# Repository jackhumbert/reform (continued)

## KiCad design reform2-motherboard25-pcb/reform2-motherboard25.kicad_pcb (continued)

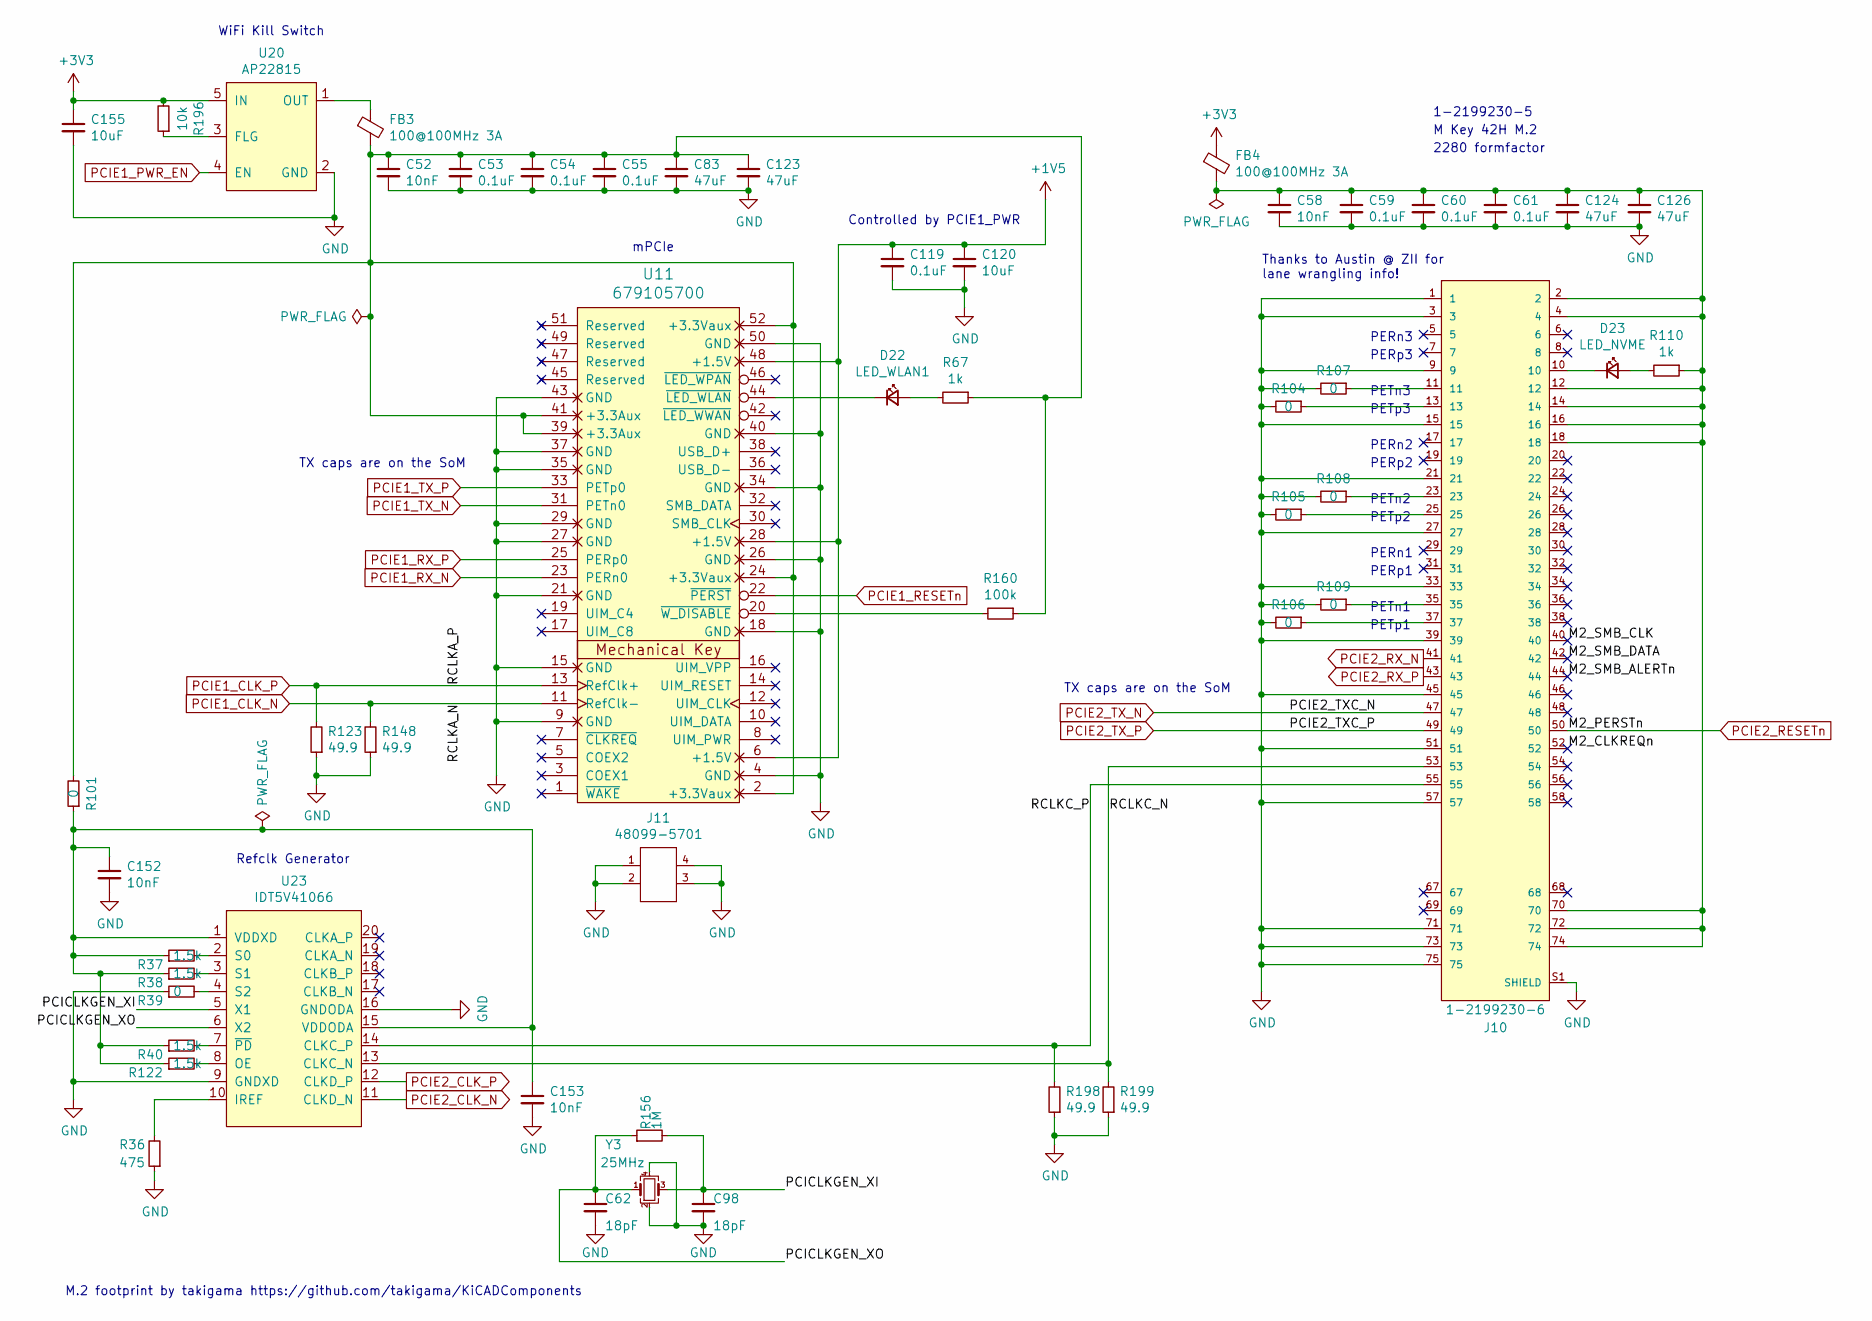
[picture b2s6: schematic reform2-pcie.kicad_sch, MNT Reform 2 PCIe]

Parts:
C52, C58, C152, C153: 10nF; C_0603_1608Metric
C53, C54, C55, C59, C60, C61, C119: 0.1uF; C_0603_1608Metric
C62, C98: 18pF; C_0603_1608Metric
C83, C123, C124, C126: 47uF; C_0603_1608Metric
C120, C155: 10uF; C_0603_1608Metric
D22: LED_WLAN1; LED_0603_1608Metric
D23: LED_NVME; LED_0603_1608Metric
FB3, FB4: 100@100MHz 3A; L_0603_1608Metric
J10: 1-2199230-6; TE_1-2199230-6
J11: 48099-5701; MOLEX_48099-5701
R36: 475; R_0603_1608Metric
R37, R38, R40, R122: 1.5k; R_0603_1608Metric
R39, R101, R104, R105, R106, R107, R108, R109: 0; R_0603_1608Metric
R67, R110: 1k; R_0603_1608Metric
R123, R148, R198, R199: 49.9; R_0603_1608Metric
R156: 1M; R_0603_1608Metric
R160: 100k; R_0603_1608Metric
R196: 10k; R_0603_1608Metric
U11: 679105700; MOLEX_67910-5700
U20: AP22815; TSOT-25
U23: IDT5V41066; TSSOP-20_4.4x6.5mm_P0.65mm
Y3: 25MHz; Crystal_SMD_Abracon_ABM8G-4Pin_3.2x2.5mm

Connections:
+1V5: C119.1, C120.1, U11.6 (+1.5V), U11.28 (+1.5V), U11.48 (+1.5V); also elsewhere on the board
+3V3: C155.1, FB4.1, R196.2, U20.5 (IN); also elsewhere on the board
/Reform 2 PCIe/M2_CLKREQn: J10.52
/Reform 2 PCIe/M2_SMB_ALERTn: J10.44
/Reform 2 PCIe/M2_SMB_CLK: J10.40
/Reform 2 PCIe/M2_SMB_DATA: J10.42
/Reform 2 PCIe/PCICLKGEN_XI: C98.1, R156.2, U23.5 (X1), Y3.3
/Reform 2 PCIe/PCICLKGEN_XO: C62.1, R156.1, U23.6 (X2), Y3.1
/Reform 2 PCIe/RCLKC_N: J10.53, R199.2, U23.13 (CLKC_N)
/Reform 2 PCIe/RCLKC_P: J10.55, R198.2, U23.14 (CLKC_P)
GND: C52.2, C53.2, C54.2, C55.2, C58.2, C59.2, C60.2, C61.2, C62.2, C83.2, C98.2, C119.2, C120.2, C123.2, C124.2, C126.2, C152.2, C153.2, C155.2, J10.1, J10.3, J10.9, J10.15, J10.21, J10.27, J10.33, J10.39, J10.45, J10.51, J10.57, J10.71, J10.73, J10.75, J10.S1 (SHIELD), J10.S2 (SHIELD), J11.1, J11.2, J11.3, J11.4, R36.1, R39.1, R104.2, R105.2, R106.2, R107.2, R108.2, R109.2, R123.1, R148.1, R198.1, R199.1, U11.4 (GND), U11.9 (GND), U11.15 (GND), U11.18 (GND), U11.21 (GND), U11.26 (GND), U11.27 (GND), U11.29 (GND), U11.34 (GND), U11.35 (GND), U11.37 (GND), U11.40 (GND), U11.43 (GND), U11.50 (GND), U20.2 (GND), U23.9 (GNDXD), U23.16 (GNDODA), Y3.2, Y3.4; also elsewhere on the board
unnamed: C52.1, C53.1, C54.1, C55.1, C83.1, C123.1, FB3.2, R67.1, R101.2, R160.1, U11.2 (+3.3Vaux), U11.24 (+3.3Vaux), U11.39 (+3.3Aux), U11.41 (+3.3Aux), U11.52 (+3.3Vaux)
unnamed: C58.1, C59.1, C60.1, C61.1, C124.1, C126.1, FB4.2, J10.2, J10.4, J10.12, J10.14, J10.16, J10.18, J10.70, J10.72, J10.74, R110.1
unnamed: C152.1, C153.1, R37.1, R38.1, R40.1, R101.1, R122.1, U23.1 (VDDXD), U23.15 (VDDODA)
unnamed: D22.1 (K), U11.44 (~LED_WLAN)
unnamed: D22.2 (A), R67.2
unnamed: D23.1 (K), J10.10
unnamed: D23.2 (A), R110.2
unnamed: J10.11, R107.1
unnamed: J10.13, R104.1
unnamed: J10.23, R108.1
unnamed: J10.25, R105.1
unnamed: J10.35, R109.1
unnamed: J10.37, R106.1
unnamed: R36.2, U23.10 (IREF)
unnamed: R37.2, U23.2 (S0)
unnamed: R38.2, U23.3 (S1)
unnamed: R39.2, U23.4 (S2)
unnamed: R40.2, U23.7 (~PD)
unnamed: R122.2, U23.8 (OE)
unnamed: R160.2, U11.20 (~W_DISABLE)
unnamed: R196.1, U20.3 (FLG)
unnamed: FB3.1, U20.1 (OUT)
PCIE1_CLK_N: R148.2, U11.11 (RefClk-); also elsewhere on the board
PCIE1_CLK_P: R123.2, U11.13 (RefClk+); also elsewhere on the board
PCIE1_PWR_EN: U20.4 (EN); also elsewhere on the board
PCIE1_RESETn: U11.22 (~PERST); also elsewhere on the board
PCIE1_RX_N: U11.23 (PERn0); also elsewhere on the board
PCIE1_RX_P: U11.25 (PERp0); also elsewhere on the board
PCIE1_TX_N: U11.31 (PETn0); also elsewhere on the board
PCIE1_TX_P: U11.33 (PETp0); also elsewhere on the board
PCIE2_CLK_N: U23.11 (CLKD_N); also elsewhere on the board
PCIE2_CLK_P: U23.12 (CLKD_P); also elsewhere on the board
PCIE2_RESETn: J10.50; also elsewhere on the board
PCIE2_RX_N: J10.41; also elsewhere on the board
PCIE2_RX_P: J10.43; also elsewhere on the board
PCIE2_TX_N: J10.47; also elsewhere on the board
PCIE2_TX_P: J10.49; also elsewhere on the board

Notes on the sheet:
1-2199230-5
Controlled by PCIE1_PWR
Thanks to Austin @ ZII for lane wrangling info!
PERp1
PERn3
TX caps are on the SoM
M.2 footprint by takigama https://github.com/takigama/KiCADComponents
PETn3
PETn1
2280 formfactor
Refclk Generator
PETp2
PETn2
PERp2
M Key 42H M.2
PERn2
mPCIe
PERp3
WiFi Kill Switch
PETp1
PERn1
PETp3

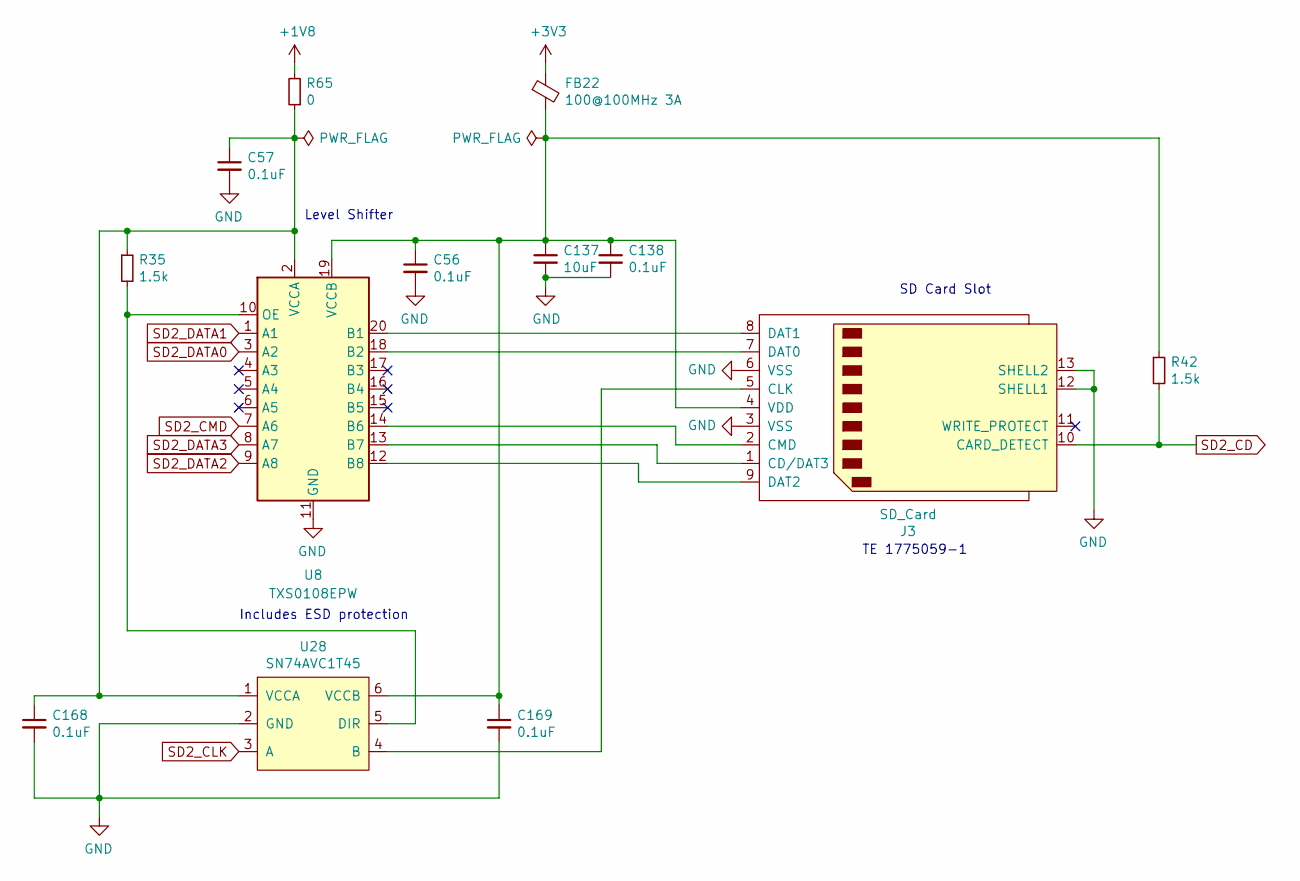
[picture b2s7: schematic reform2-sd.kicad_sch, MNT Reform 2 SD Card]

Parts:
C56, C57, C138, C168, C169: 0.1uF; C_0603_1608Metric
C137: 10uF; C_0603_1608Metric
FB22: 100@100MHz 3A; L_0603_1608Metric
J3: SD_Card; TE_1775059-1
R35, R42: 1.5k; R_0603_1608Metric
R65: 0; R_0603_1608Metric
U8: TXS0108EPW; TSSOP-20_4.4x6.5mm_P0.65mm
U28: SN74AVC1T45; SOT-23-6

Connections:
+1V8: R65.2; also elsewhere on the board
+3V3: FB22.1; also elsewhere on the board
GND: C56.2, C57.2, C137.2, C138.2, C168.2, C169.2, J3.3 (VSS), J3.6 (VSS), J3.12 (SHELL1), J3.13 (SHELL2), U8.11 (GND), U28.2 (GND); also elsewhere on the board
unnamed: C56.1, C137.1, C138.1, C169.1, FB22.2, J3.4 (VDD), R42.1, U8.19 (VCCB), U28.6 (VCCB)
unnamed: C57.1, C168.1, R35.1, R65.1, U8.2 (VCCA), U28.1 (VCCA)
unnamed: J3.1 (CD/DAT3), U8.13 (B7)
unnamed: J3.2 (CMD), U8.14 (B6)
unnamed: J3.5 (CLK), U28.4 (B)
unnamed: J3.7 (DAT0), U8.18 (B2)
unnamed: J3.8 (DAT1), U8.20 (B1)
unnamed: J3.9 (DAT2), U8.12 (B8)
unnamed: R35.2, U8.10 (OE), U28.5 (DIR)
SD2_CD: J3.10 (CARD_DETECT), R42.2; also elsewhere on the board
SD2_CLK: U28.3 (A); also elsewhere on the board
SD2_CMD: U8.7 (A6); also elsewhere on the board
SD2_DATA0: U8.3 (A2); also elsewhere on the board
SD2_DATA1: U8.1 (A1); also elsewhere on the board
SD2_DATA2: U8.9 (A8); also elsewhere on the board
SD2_DATA3: U8.8 (A7); also elsewhere on the board

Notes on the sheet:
TE 1775059-1
SD Card Slot
Level Shifter
Includes ESD protection

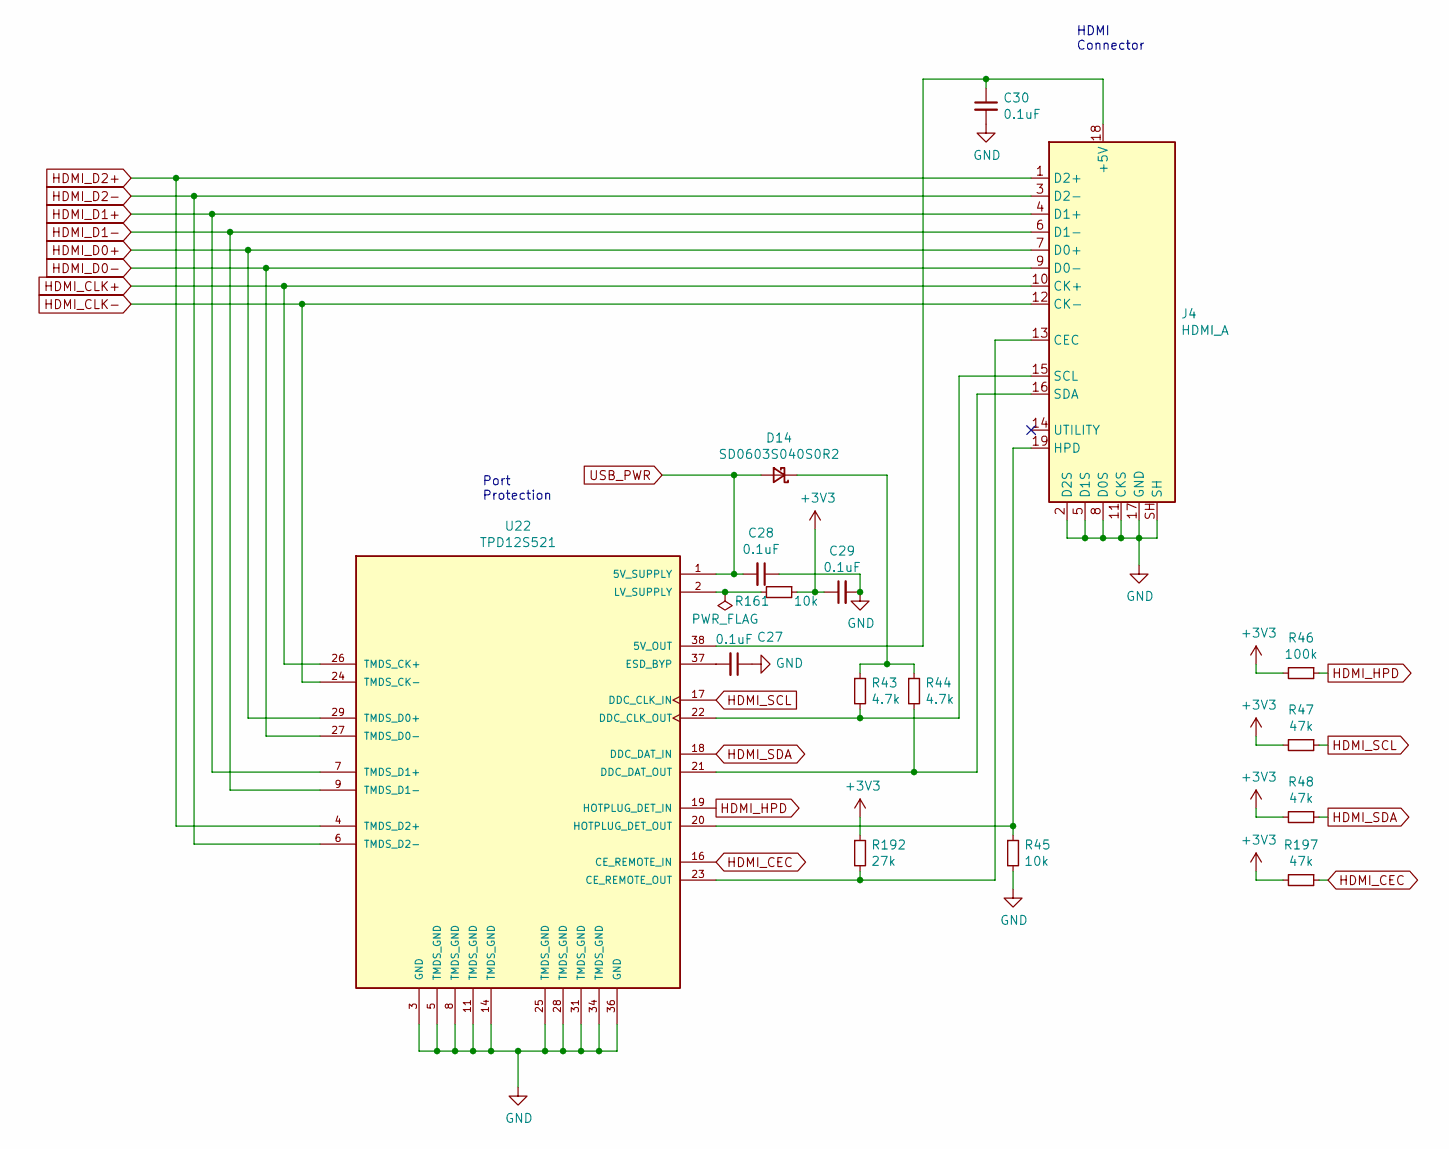
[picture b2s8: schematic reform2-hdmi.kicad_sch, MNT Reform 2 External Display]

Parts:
C27, C28, C29, C30: 0.1uF; C_0603_1608Metric
D14: SD0603S040S0R2; D_0603_1608Metric_Castellated
J4: HDMI_A; HDMI-685119134923
R43, R44: 4.7k; R_0603_1608Metric
R45, R161: 10k; R_0603_1608Metric
R46: 100k; R_0603_1608Metric
R47, R48, R197: 47k; R_0603_1608Metric
R192: 27k; R_0603_1608Metric
U22: TPD12S521; TSSOP50P640X120-38N

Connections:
+3V3: C29.1, R46.2, R47.2, R48.2, R161.1, R192.1, R197.2; also elsewhere on the board
GND: C27.1, C28.1, C29.2, C30.2, J4.2 (D2S), J4.5 (D1S), J4.8 (D0S), J4.11 (CKS), J4.17 (GND), J4.SH, R45.2, U22.3 (GND), U22.5 (TMDS_GND), U22.8 (TMDS_GND), U22.11 (TMDS_GND), U22.14 (TMDS_GND), U22.25 (TMDS_GND), U22.28 (TMDS_GND), U22.31 (TMDS_GND), U22.34 (TMDS_GND), U22.36 (GND); also elsewhere on the board
HDMI_CEC: R197.1, U22.16 (CE_REMOTE_IN); also elsewhere on the board
HDMI_CLK+: J4.10 (CK+), U22.13 (TMDS_CK+), U22.26 (TMDS_CK+); also elsewhere on the board
HDMI_CLK-: J4.12 (CK-), U22.15 (TMDS_CK-), U22.24 (TMDS_CK-); also elsewhere on the board
HDMI_D0+: J4.7 (D0+), U22.10 (TMDS_D0+), U22.29 (TMDS_D0+); also elsewhere on the board
HDMI_D0-: J4.9 (D0-), U22.12 (TMDS_D0-), U22.27 (TMDS_D0-); also elsewhere on the board
HDMI_D1+: J4.4 (D1+), U22.7 (TMDS_D1+), U22.32 (TMDS_D1+); also elsewhere on the board
HDMI_D1-: J4.6 (D1-), U22.9 (TMDS_D1-), U22.30 (TMDS_D1-); also elsewhere on the board
HDMI_D2+: J4.1 (D2+), U22.4 (TMDS_D2+), U22.35 (TMDS_D2+); also elsewhere on the board
HDMI_D2-: J4.3 (D2-), U22.6 (TMDS_D2-), U22.33 (TMDS_D2-); also elsewhere on the board
HDMI_HPD: R46.1, U22.19 (HOTPLUG_DET_IN); also elsewhere on the board
HDMI_SCL: R47.1, U22.17 (DDC_CLK_IN); also elsewhere on the board
HDMI_SDA: R48.1, U22.18 (DDC_DAT_IN); also elsewhere on the board
unnamed: C27.2, U22.37 (ESD_BYP)
unnamed: C30.1, J4.18 (+5V), U22.38 (5V_OUT)
unnamed: D14.1 (K), R43.1, R44.1
unnamed: J4.13 (CEC), R192.2, U22.23 (CE_REMOTE_OUT)
unnamed: J4.15 (SCL), R43.2, U22.22 (DDC_CLK_OUT)
unnamed: J4.16 (SDA), R44.2, U22.21 (DDC_DAT_OUT)
unnamed: J4.19 (HPD), R45.1, U22.20 (HOTPLUG_DET_OUT)
unnamed: R161.2, U22.2 (LV_SUPPLY)
USB_PWR: C28.2, D14.2 (A), U22.1 (5V_SUPPLY); also elsewhere on the board

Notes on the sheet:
HDMI Connector
Port Protection

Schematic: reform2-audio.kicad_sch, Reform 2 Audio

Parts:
C127, C147: 220uF; C_1210_3225Metric
C139, C151, C170: 4.7uF; C_0603_1608Metric
C141, C162, C163: 1uF; C_0603_1608Metric
C142, C143, C144, C154, C156, C158, C165, C166: 0.1uF; C_0603_1608Metric
C150: 10uF; C_0603_1608Metric
C157, C159: 470nF; C_0603_1608Metric
D10: SP0503BAHT; SOT-143
FB10, FB11, FB16, FB17, FB18, FB19, FB20, FB21: 100@100MHz 3A; L_0603_1608Metric
J7: SJ-43516-SMT
J16: LINE_IN; PinHeader_1x03_P2.00mm_Vertical
J21: Conn_01x04; JST_PH_B4B-PH-K_1x04_P2.00mm_Vertical
L8, L9, L10, L11: 15uH; L_1210_3225Metric
R66, R112: 220; R_0603_1608Metric
R114, R121, R138, R139, R150, R151: 33; R_0603_1608Metric
R135, R136: 4.7k; R_0603_1608Metric
R140: 680; R_0603_1608Metric
R141, R152, R187: 0; R_0603_1608Metric
R142, R143, R144: 47k; R_0603_1608Metric
U3: WM8960; QFN-32-1EP_5x5mm_P0.5mm_EP3.45x3.45mm_ThermalVias

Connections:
+3V3: FB18.1, FB20.1, FB21.1, R135.1, R136.1, R187.1; also elsewhere on the board
DAC_BCLK: R114.1; also elsewhere on the board
DAC_DIN: R150.1; also elsewhere on the board
DAC_DOUT: R121.1; also elsewhere on the board
DAC_MCLK: R138.2; also elsewhere on the board
DAC_RXFS: R139.1; also elsewhere on the board
DAC_SCL: R66.1; also elsewhere on the board
DAC_SDA: R112.1; also elsewhere on the board
DAC_TXFS: R151.1; also elsewhere on the board
GND: C139.2, C142.2, C143.2, C144.1, C150.2, C151.2, C154.2, C156.2, C158.2, C165.2, C166.2, C170.2, D10.1 (A), J7.4 (RING2), J16.1, R142.2, R143.2, U3.9 (DGND), U3.20 (SPKGND2), U3.24 (SPKGND1), U3.28 (AGND), U3.33 (GND); also elsewhere on the board
unnamed: C127.1, D10.3 (K), J7.2 (TIP), R142.1
unnamed: C127.2, U3.31 (HP_L)
unnamed: C139.1, C151.1, FB19.2, U3.21 (SPKVDD2), U3.26 (SPKVDD1)
unnamed: C141.1, D10.2 (K), J7.1 (SLEEVE), R140.2
unnamed: C141.2, U3.4 (LINPUT1)
unnamed: C142.1, FB21.2, U3.32 (AVDD)
unnamed: C143.1, FB20.2, R144.1, U3.10 (DBVDD)
unnamed: C144.2, FB18.2, U3.8 (DCVDD)
unnamed: C147.1, D10.4 (K), J7.3 (RING1), R143.1
unnamed: C147.2, U3.29 (HP_R)
unnamed: C150.1, C154.1, U3.27 (VMID)
unnamed: C156.1, C157.1, J21.4, L8.2
unnamed: C157.2, C158.1, J21.3, L9.2
unnamed: C159.1, C165.1, J21.2, L10.2
unnamed: C159.2, C166.1, J21.1, L11.2
unnamed: C162.1, U3.3 (LINPUT2)
unnamed: C162.2, J16.3
unnamed: C163.1, U3.6 (RINPUT2)
unnamed: C163.2, J16.2
unnamed: C170.1, R140.1, U3.1 (MICBIAS)
unnamed: J7.6 (RING_SWITCH), R141.1, R144.2
unnamed: FB10.2, L8.1
unnamed: FB11.2, L9.1
unnamed: FB16.2, L10.1
unnamed: FB17.2, L11.1
unnamed: R112.2, R136.2, U3.18 (SDIN)
unnamed: R114.2, U3.12 (BCLK)
unnamed: R121.2, U3.14 (DACDAT)
unnamed: R66.2, R135.2, U3.17 (SCLK)
unnamed: R138.1, U3.11 (MCLK)
unnamed: R139.2, U3.15 (ADCLRC)
unnamed: R141.2, U3.2 (LINPUT3)
unnamed: R150.2, U3.16 (ADCDAT)
unnamed: R151.2, U3.13 (DACLRC)
unnamed: FB19.1, R152.2, R187.2
unnamed: FB17.1, U3.19 (SPK_RN)
unnamed: FB16.1, U3.22 (SPK_RP)
unnamed: FB11.1, U3.23 (SPK_LN)
unnamed: FB10.1, U3.25 (SPK_LP)
USB_PWR: R152.1; also elsewhere on the board

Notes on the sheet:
CTIA standard TRRS
butterworth filter with 40khz cutoff: speaker ohms = 8 L = 22.5uH C = 0.35uF
Jack Detect
Audio Codec
Speakers: PUI AS01808AO-3-R 8 Ohm 1 W
NOSTUFF
NOTE: DCVDD could be 1.8v
more bass!
800mA

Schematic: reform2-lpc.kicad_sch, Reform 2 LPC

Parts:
BT1: CR1220; BatteryHolder_Keystone_3000_1x12mm
C46, C47: 10uF; C_0603_1608Metric
C48, C51: 18pF; C_0603_1608Metric
C49, C50, C140: 0.1uF; C_0603_1608Metric
J8: USB_C_Receptacle_USB2.0; USB_C_Receptacle_HRO_TYPE-C-31-M-12
J22: LPC_IO; PinHeader_2x08_P2.54mm_Vertical
J23: KDBSYSCTL; JST_PH_B4B-PH-K_1x04_P2.00mm_Vertical
R68, R69: 4.7k; R_0603_1608Metric
R70, R72: 33; R_0603_1608Metric
R71, R195: 1.5k; R_0603_1608Metric
R73, R74, R75, R76, R124, R125, R126, R137, R157, R194: 0; R_0603_1608Metric
R128: 10k; R_0603_1608Metric
SW1: SW_DIP_x01; SW_DIP_SPSTx01_Slide_Omron_A6S-110x_W8.9mm_P2.54mm
SW2: SW_Push; UK-B0206-G3.8-250-JZ
U5: PCF8523T; SOIC-8_3.9x4.9mm_P1.27mm
U18: LPC11U24FBD48-301; LQFP-48_7x7mm_P0.5mm
Y2: 12MHz; Crystal_SMD_Abracon_ABM8G-4Pin_3.2x2.5mm
Y4: 32.768 kHz; Crystal_SMD_3215-2Pin_3.2x1.5mm

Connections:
1V2_PWR_EN: U18.2 (PIO1_19); also elsewhere on the board
3V3_PWR_EN: U18.48 (PIO1_16); also elsewhere on the board
5V_PWR_EN: U18.43 (PIO1_15); also elsewhere on the board
/Reform 2 Power/Reform 2 LPC/LPCUD_N: R72.2, U18.19 (USB_DM)
/Reform 2 Power/Reform 2 LPC/LPCUD_P: R70.2, U18.20 (USB_DP)
/Reform 2 Power/Reform 2 LPC/LPC_AD5: J22.7, U18.40 (PIO0_16)
/Reform 2 Power/Reform 2 LPC/LPC_AD7: J22.10, U18.42 (PIO0_23)
/Reform 2 Power/Reform 2 LPC/LPC_MISO0: R124.1, U18.27 (PIO0_8)
/Reform 2 Power/Reform 2 LPC/LPC_MISO1a: J22.2, U18.30 (PIO0_22)
/Reform 2 Power/Reform 2 LPC/LPC_MISO1b: R74.2, U18.26 (PIO1_21)
/Reform 2 Power/Reform 2 LPC/LPC_MOSI0: R125.1, U18.28 (PIO0_9)
/Reform 2 Power/Reform 2 LPC/LPC_MOSI1a: J22.14, U18.17 (PIO0_21)
/Reform 2 Power/Reform 2 LPC/LPC_MOSI1b: R75.2, U18.38 (PIO1_22)
/Reform 2 Power/Reform 2 LPC/LPC_RXDa: J22.12, U18.46 (PIO0_18)
/Reform 2 Power/Reform 2 LPC/LPC_RXDc: J23.3, U18.11 (PIO1_26)
/Reform 2 Power/Reform 2 LPC/LPC_SCK0a: R126.1, U18.29 (PIO0_10)
/Reform 2 Power/Reform 2 LPC/LPC_SCK0b: J22.1, U18.31 (PIO1_29)
/Reform 2 Power/Reform 2 LPC/LPC_SCK1b: R73.2, U18.13 (PIO1_20)
/Reform 2 Power/Reform 2 LPC/LPC_SCLKa: J22.9, U18.45 (PIO0_17)
/Reform 2 Power/Reform 2 LPC/LPC_SCLKc: R194.2, U18.24 (PIO1_28)
/Reform 2 Power/Reform 2 LPC/LPC_SSEL0: R157.1, U18.10 (PIO0_2)
/Reform 2 Power/Reform 2 LPC/LPC_SSEL1: R76.2, U18.18 (PIO1_23)
/Reform 2 Power/Reform 2 LPC/LPC_SWDIO: J22.8, U18.39 (PIO0_15)
/Reform 2 Power/Reform 2 LPC/LPC_TDI: J22.4, U18.32 (PIO0_11)
/Reform 2 Power/Reform 2 LPC/LPC_TDO: J22.6, U18.34 (PIO0_13)
/Reform 2 Power/Reform 2 LPC/LPC_TMS: J22.3, U18.33 (PIO0_12)
/Reform 2 Power/Reform 2 LPC/LPC_TXDa: J22.11, U18.47 (PIO0_19)
/Reform 2 Power/Reform 2 LPC/LPC_TXDc: J23.2, U18.12 (PIO1_27)
/Reform 2 Power/Reform 2 LPC/LPC_UFTOGG: SW1.2, U18.4 (PIO0_1)
/Reform 2 Power/Reform 2 LPC/LPC_UVBUS: R195.2, U18.14 (PIO0_3)
/Reform 2 Power/Reform 2 LPC/LPC_~RESET: SW2.2, U18.3 (PIO0_0)
/Reform 2 Power/Reform 2 LPC/LPC_~TRST: J22.5, U18.35 (PIO0_14)
/Reform 2 Power/Reform 2 LPC/LPC_~USBCON: J22.13, U18.22 (PIO0_6)
AUX_PWR_EN: U18.23 (PIO0_7); also elsewhere on the board
BMON_CS: R76.1; also elsewhere on the board
BMON_SCK: R73.1; also elsewhere on the board
BMON_SDI: R75.1; also elsewhere on the board
BMON_SDO: R74.1, R128.1; also elsewhere on the board
CHG_RNG: U18.1 (PIO1_25); also elsewhere on the board
DAC_SCL: U5.6 (SCL); also elsewhere on the board
DAC_SDA: U5.5 (SDA); also elsewhere on the board
GND: BT1.2 (-), C46.2, C47.2, C48.2, C49.2, C50.2, C51.2, C140.1, J8.A1 (GND), J8.A12 (GND), J8.B1 (GND), J8.B12 (GND), J8.S1 (SHIELD), J22.16, J23.4, SW1.1, SW2.1, U5.4 (VSS), U18.5 (VSS), U18.41 (VSS), Y2.2, Y2.4; also elsewhere on the board
IMX_RESETn: R194.1; also elsewhere on the board
IMX_RTC_IRQ: R137.1; also elsewhere on the board
IMX_WAKE: U18.21 (PIO1_24); also elsewhere on the board
INA_SCL: R69.2, U18.15 (PIO0_4); also elsewhere on the board
INA_SDA: R68.2, U18.16 (PIO0_5); also elsewhere on the board
LPC_MISO: R124.2; also elsewhere on the board
LPC_MOSI: R125.2; also elsewhere on the board
LPC_SCK: R126.2; also elsewhere on the board
LPC_SS0: R157.2; also elsewhere on the board
LPC_UART2_RX: U18.37 (PIO1_14); also elsewhere on the board
LPC_UART2_TX: U18.36 (PIO1_13); also elsewhere on the board
LPC_VCC: C46.1, C47.1, C49.1, C50.1, C140.2, J22.15, J23.1, R68.1, R69.1, R71.1, R128.2, R195.1, U5.8 (VDD), U18.8 (VDD), U18.44 (VDD); also elsewhere on the board
unnamed: BT1.1 (+), U5.3 (VBAT)
unnamed: C48.1, U18.7 (XTALOUT), Y2.1
unnamed: C51.1, U18.6 (XTALIN), Y2.3
unnamed: J8.A6 (D+), J8.B6 (D+), R70.1, R71.2
unnamed: J8.A7 (D-), J8.B7 (D-), R72.1
unnamed: R137.2, U5.7 (~INT1/CLKOUT)
unnamed: U5.1 (OSCI), Y4.1
unnamed: U5.2 (OSCO), Y4.2
PCIE1_PWR_EN: U18.9 (PIO0_20); also elsewhere on the board
USB_PWR_EN: U18.25 (PIO1_31); also elsewhere on the board

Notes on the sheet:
TODO: check CCs
System Controller
Expansion Port
I2C lines pulled up by SYS 3v3 power near DAC
Power Switches
Keyboard System Control Port (SYSCTL)
Powered by coin cell when batteries removed
Powered by main batteries in standby
Realtime Clock

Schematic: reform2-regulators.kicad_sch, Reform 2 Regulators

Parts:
C3: 0.33uF; C_0603_1608Metric
C16, C17: 100uF; CP_Elec_8x10
C18, C19: 220uF; CP_Elec_8x10
C33, C35: 4.7uF; C_0603_1608Metric
C34, C37: 10uF; C_0603_1608Metric
C36, C38: 6.8pF; C_0603_1608Metric
C82: 2.2uF; C_0603_1608Metric
C121: 47uF; C_0603_1608Metric
C128, C148: 10nF; C_0603_1608Metric
C129, C130, C145, C146: 1uF; C_0603_1608Metric
D3: SBR0560S1; D_SOD-123
D11: LED3V; LED_0603_1608Metric
D12: LED5V; LED_0603_1608Metric
D15, D16: BZX584C3V3-G3-08; D_SOD-523
D20, D21: SK54A-LTP; D_SMA
L3, L4: 68uH; L_Bourns_SRR1210A
L5: 10uH; L_1210_3225Metric
L6, L7: 2.2uH; L_1210_3225Metric
R1: 1M; R_0603_1608Metric
R33, R164: 1k; R_0603_1608Metric
R53, R57: 51k; R_0603_1608Metric
R58: 68k; R_0603_1608Metric
R98, R100, R185, R186: 0; R_0603_1608Metric
R178, R179, R181, R188, R189: 100k; R_0603_1608Metric
R180: 150k; R_0603_1608Metric
U7: LM2677SX-5; TO-263-7_TabPin8
U12: LM2677SX-3.3; TO-263-7_TabPin8
U13, U19: TLV62568DBV; SOT-23-5
U14: LMR16006YQ3; TSOT-23-6
U17: TLV1117-18; SOT-223

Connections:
1V2_PWR_EN: R185.1; also elsewhere on the board
3V3_PWR_AUX: R98.2; also elsewhere on the board
3V3_PWR_EN: D16.1 (K), R57.2, U12.7 (ON/~OFF); also elsewhere on the board
5V_PWR_EN: D15.1 (K), R53.2, U7.7 (ON/~OFF); also elsewhere on the board
30V_GATE: C16.1, C17.1, C82.2, C145.2, C146.2, R1.2, U7.2 (VIN), U12.2 (VIN), U14.5 (VIN); also elsewhere on the board
+1V2: C36.1, C37.1, L6.2, R178.1; also elsewhere on the board
+1V5: C34.1, C38.1, L7.2, R180.1; also elsewhere on the board
+1V8: C130.1, U17.2 (VO); also elsewhere on the board
+3V3: C19.1, D11.2 (A), L4.2, R100.2, U12.6 (FB); also elsewhere on the board
+5V: C18.1, C33.1, C35.1, D12.2 (A), L3.2, U7.6 (FB), U13.4 (VIN), U19.4 (VIN); also elsewhere on the board
GND: C16.2, C17.2, C18.2, C19.2, C33.2, C34.2, C35.2, C37.2, C82.1, C121.1, C129.2, C130.2, C145.1, C146.1, D3.2 (A), D15.2 (A), D16.2 (A), D20.2 (A), D21.2 (A), R33.1, R53.1, R57.1, R58.2, R164.1, R179.2, R181.2, R188.2, R189.2, U7.4 (GND), U7.8 (PAD), U12.4 (GND), U12.8 (PAD), U13.2 (GND), U14.2 (GND), U17.1 (GND), U19.2 (GND); also elsewhere on the board
LPC_VCC: C121.2, L5.2, U14.3 (FB); also elsewhere on the board
unnamed: C3.1, D3.1 (K), L5.1, U14.6 (SW)
unnamed: C3.2, U14.1 (BOOST)
unnamed: C36.2, R178.2, R179.1, U13.5 (FB)
unnamed: C38.2, R180.2, R181.1, U19.5 (FB)
unnamed: C128.1, D21.1 (K), L4.1, U12.1 (VSW)
unnamed: C128.2, U12.3 (CB)
unnamed: C129.1, R98.1, R100.1, U17.3 (VI)
unnamed: C148.1, D20.1 (K), L3.1, U7.1 (VSW)
unnamed: C148.2, U7.3 (CB)
unnamed: D11.1 (K), R33.2
unnamed: D12.1 (K), R164.2
unnamed: L6.1, U13.3 (SW)
unnamed: L7.1, U19.3 (SW)
unnamed: R1.1, R58.1, U14.4 (EN)
unnamed: R185.2, R188.1, U13.1 (EN)
unnamed: R186.2, R189.1, U19.1 (EN)
PCIE1_PWR_EN: R186.1; also elsewhere on the board

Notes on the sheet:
Standby always-on 3V3 power rail
Power LEDs
TODO: test new UVLO <20V
NOSTUFF
Up to 1A (peak) 375mA normal from mPCIe
Up to 70mA consumed by DSI bridge
Up to 780mA (!) consumed by USB hub
Up to 5A @ 5V
TODO: test these!
Up to 5A @ 3.3V
VCCIO supply for DSI + SD
Up to 40mA consumed by DSI bridge and SD card level shifter
Main system power converters, enabled by LPC

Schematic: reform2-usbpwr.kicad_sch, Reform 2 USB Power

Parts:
C164, C167: 10uF; C_0603_1608Metric
R2, R83: 10k; R_0603_1608Metric
U24, U27: AP22815; TSOT-25

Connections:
3V3_PWR_AUX: U27.1 (OUT); also elsewhere on the board
+3V3: C167.1, R2.2, U27.5 (IN); also elsewhere on the board
+5V: C164.1, R83.2, U24.5 (IN); also elsewhere on the board
AUX_PWR_EN: U27.4 (EN); also elsewhere on the board
GND: C164.2, C167.2, U24.2 (GND), U27.2 (GND); also elsewhere on the board
unnamed: R2.1, U27.3 (FLG)
unnamed: R83.1, U24.3 (FLG)
USB_PWR: U24.1 (OUT); also elsewhere on the board
USB_PWR_EN: U24.4 (EN); also elsewhere on the board

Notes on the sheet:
3V3 Aux Power Switch
USB Power Switch

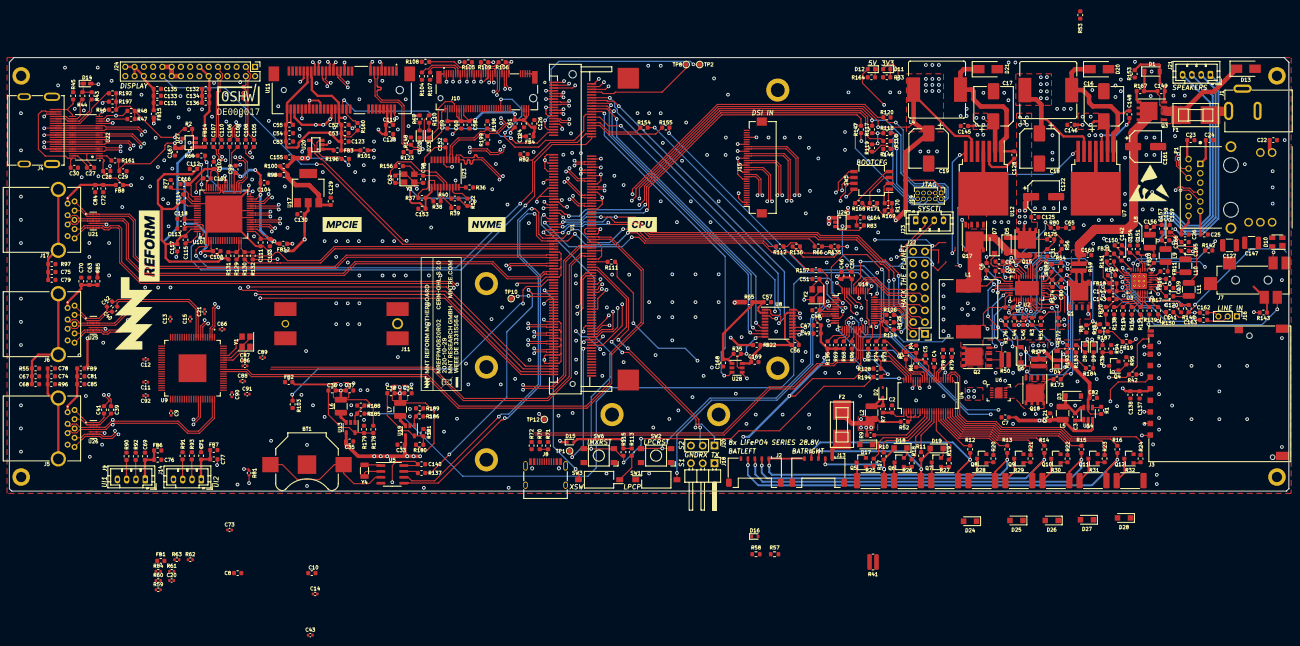
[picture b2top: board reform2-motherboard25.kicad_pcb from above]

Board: 6 copper layers, 276.0 x 93.5 mm, 504 parts (0 on the bottom side), 439 nets.

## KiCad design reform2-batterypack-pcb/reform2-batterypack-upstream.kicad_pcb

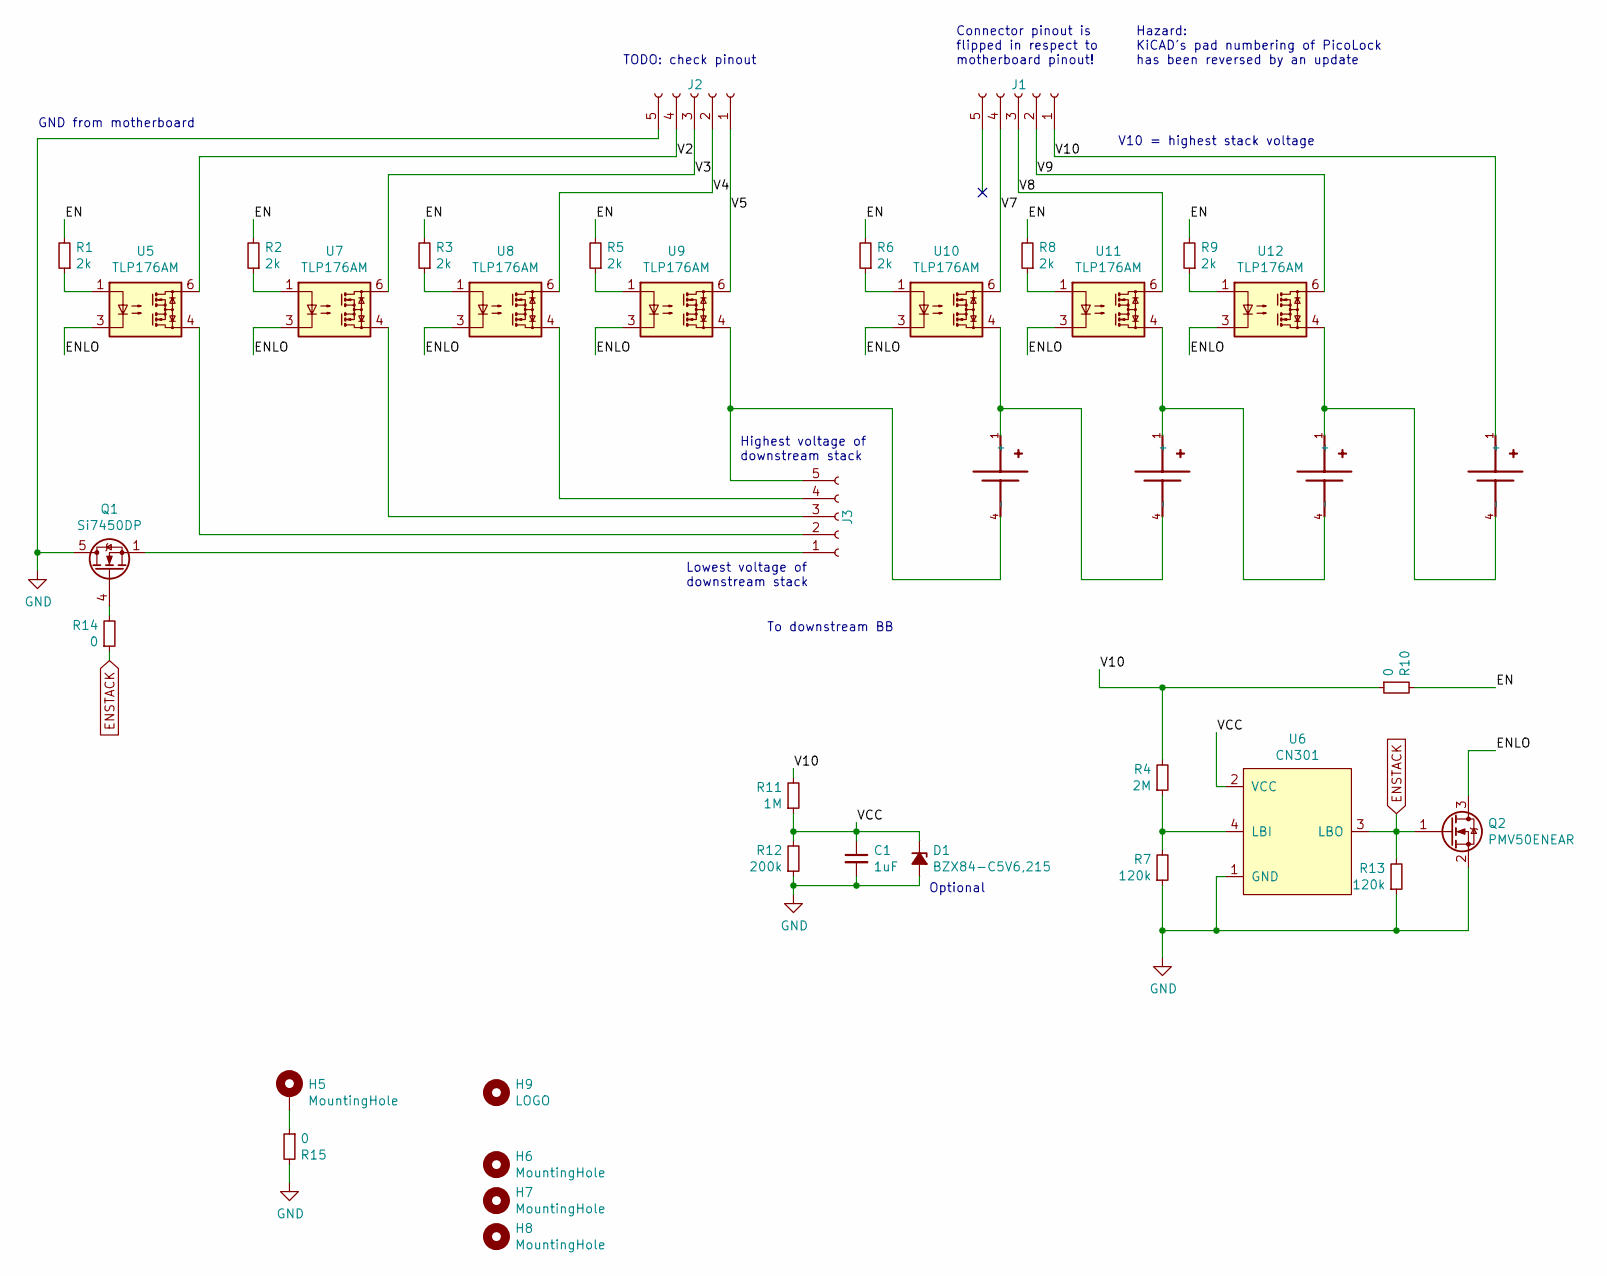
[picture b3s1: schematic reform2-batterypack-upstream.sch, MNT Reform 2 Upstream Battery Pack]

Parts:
C1: 1uF; C_0603_1608Metric
D1: BZX84-C5V6,215; D_SOT-23_ANK
H5, H6, H7, H8: MountingHole; MountingHole_2.2mm_M2
H9: LOGO; reform2-batterypack-badge-d5
J1, J2, J3: Conn_01x05_Female; Molex_Pico-Lock_504050-0591_1x05-1MP_P1.50mm_Horizontal
Q1: Si7450DP; PowerPAK_SO-8_Single
Q2: PMV50ENEAR; SOT-23
R1, R2, R3, R5, R6, R8, R9: 2k; R_0603_1608Metric
R4: 2M; R_0603_1608Metric
R7, R13: 120k; R_0603_1608Metric
R10, R14, R15: 0; R_0603_1608Metric
R11: 1M; R_0603_1608Metric
R12: 200k; R_0603_1608Metric
U1, U2, U3, U4: KEYSTONE_54; Keystone54
U5, U7, U8, U9, U10, U11, U12: TLP176AM; MFSOP6-4_4.4x3.6mm_P1.27mm
U6: CN301; SOT-23-5

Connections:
/EN: R1.2, R2.2, R3.2, R5.2, R6.2, R8.2, R9.2, R10.2
/ENLO: Q2.3 (D), U5.3, U7.3, U8.3, U9.3, U10.3, U11.3, U12.3
/V2: J2.4, U5.6
/V3: J2.3, U7.6
/V4: J2.2, U8.6
/V5: J2.1, U9.6
/V7: J1.4, U10.6
/V8: J1.3, U11.6
/V9: J1.2, U12.6
/V10: J1.1, R4.2, R10.1, R11.2, U4.1 (+), U4.2 (+), U4.3 (+)
/VCC: C1.1, D1.1 (K), R11.1, R12.2, U6.2 (VCC)
ENSTACK: Q1.4 (G), Q2.1 (G), R13.2, R14.1, R14.2, U6.3 (LBO)
GND: C1.2, D1.2 (A), J2.5, Q1.5 (D), Q2.2 (S), R7.1, R12.1, R13.1, R15.2, U6.1 (GND)
unnamed: J3.1, Q1.1 (S), Q1.2 (S), Q1.3 (S)
unnamed: J3.2, U5.4
unnamed: J3.3, U7.4
unnamed: J3.4, U8.4
unnamed: J3.5, U1.4 (-), U1.5 (-), U1.6 (-), U9.4
unnamed: R1.1, U5.1
unnamed: R2.1, U7.1
unnamed: R3.1, U8.1
unnamed: R4.1, R7.2, U6.4 (LBI)
unnamed: R5.1, U9.1
unnamed: R6.1, U10.1
unnamed: R8.1, U11.1
unnamed: R9.1, U12.1
unnamed: H5.1, R15.1
unnamed: U1.1 (+), U1.2 (+), U1.3 (+), U2.4 (-), U2.5 (-), U2.6 (-), U10.4
unnamed: U2.1 (+), U2.2 (+), U2.3 (+), U3.4 (-), U3.5 (-), U3.6 (-), U11.4
unnamed: U3.1 (+), U3.2 (+), U3.3 (+), U4.4 (-), U4.5 (-), U4.6 (-), U12.4

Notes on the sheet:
Connector pinout is flipped in respect to motherboard pinout!
V10 = highest stack voltage
To downstream BB
TODO: check pinout
GND from motherboard
Lowest voltage of downstream stack
Highest voltage of downstream stack
Optional
Hazard: KiCAD's pad numbering of PicoLock has been reversed by an update

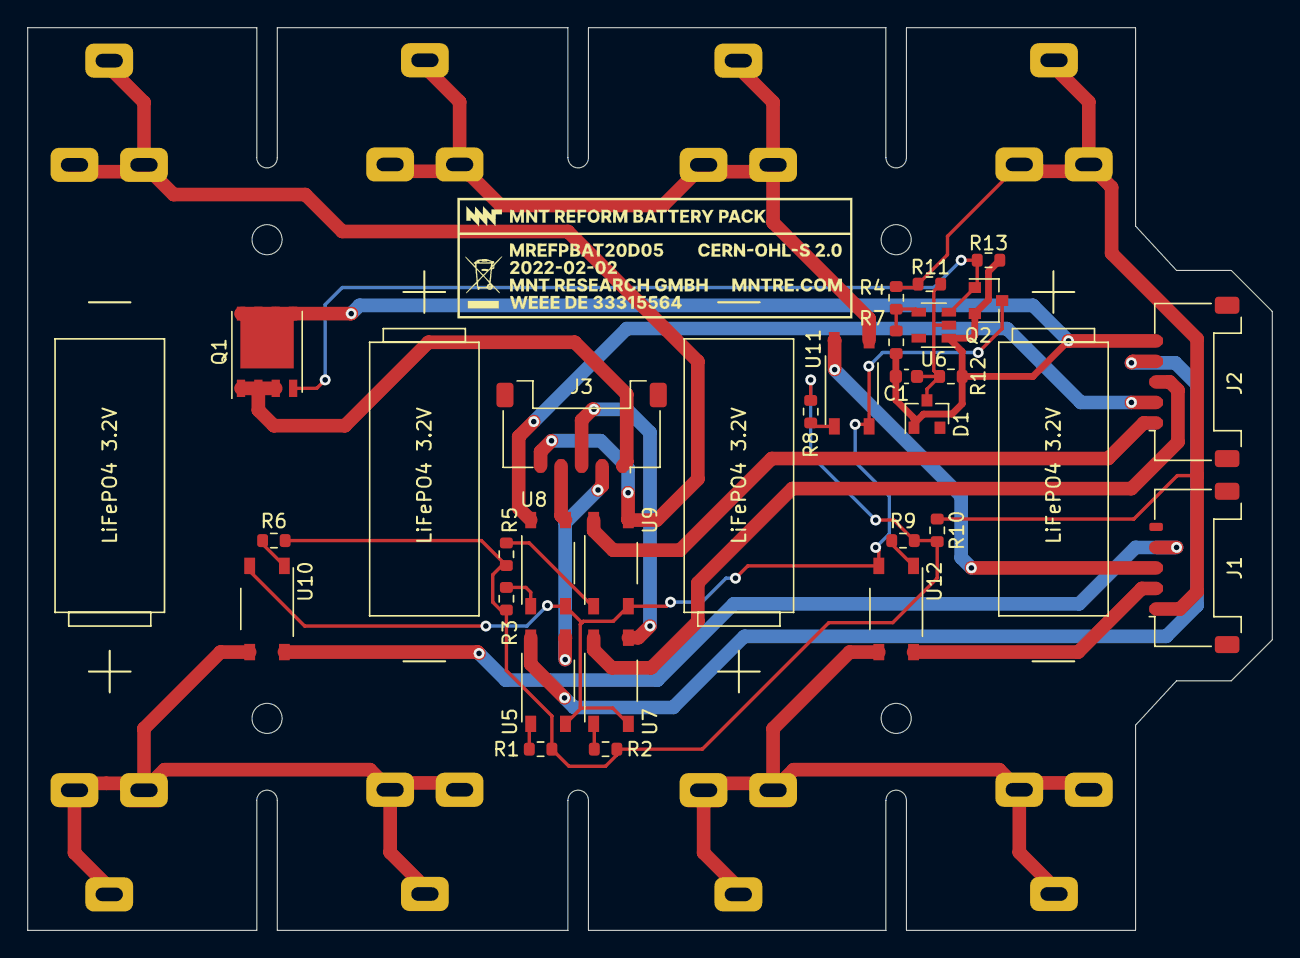
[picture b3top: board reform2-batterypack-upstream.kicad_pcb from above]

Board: 2 copper layers, 91.0 x 66.0 mm, 37 parts (0 on the bottom side), 29 nets.
